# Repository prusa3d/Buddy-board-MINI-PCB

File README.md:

# Buddy-board-MINI-PCB

KiCad PCB layout

* [Interactive bom](http://htmlpreview.github.io/?https://github.com/prusa3d/Buddy-board-MINI-PCB/blob/master/rev.1.0.0/ibom.html)
* [STEP 3D model](rev.1.0.0/BUDDY_v1.0.0.step)

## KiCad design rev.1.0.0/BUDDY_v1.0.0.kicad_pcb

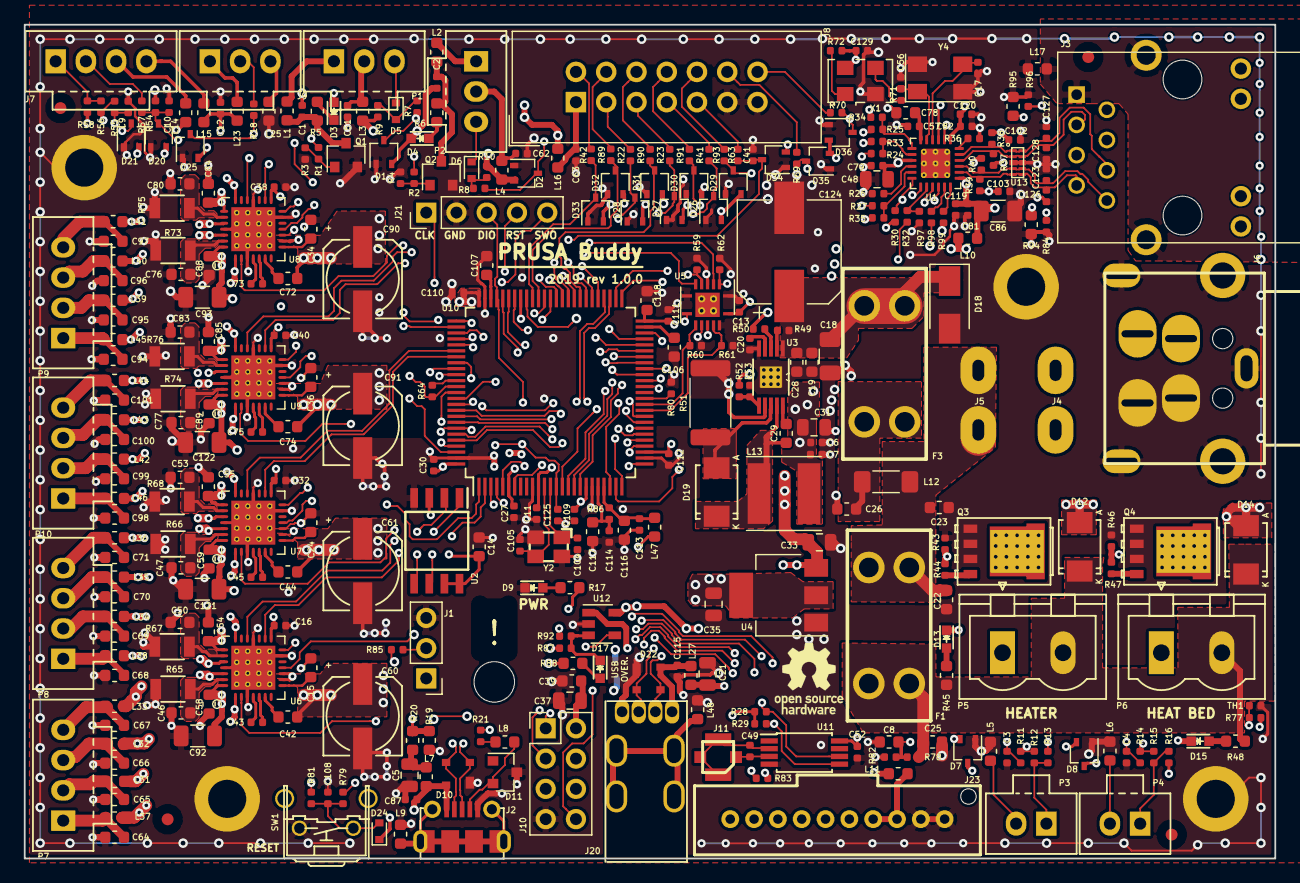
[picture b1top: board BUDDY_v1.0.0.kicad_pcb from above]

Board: 6 copper layers, 105.0 x 70.0 mm, 362 parts (1 on the bottom side), 245 nets.

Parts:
C1, C2, C3, C4, C6, C7, C9, C10, C11, C12, C13, C16, C27, C30, C32, C38, C40, C41, C51, C52, C62, C63, C79, C87, C102, C103, C108, C109, C110, C111, C112, C113, C114, C115, C119, C120, C125: 100n; C_0402_1005Metric
C5: 10u*; C_0805_2012Metric
C8, C14, C22, C23, C25, C26, C28, C29, C39, C42, C44, C46, C47, C50, C53, C54, C55, C58, C59, C72, C74, C76, C77, C80, C83, C84, C85, C88, C89: 100n; C_0603_1608Metric
C15, C24, C34, C36: 4.7uF; C_0603_1608Metric
C17, C56: 30p; C_0402_1005Metric
C18: 4u7; C_1206_3216Metric
C19, C78, C117: 1u; C_0603_1608Metric
C20: 4n7; C_0402_1005Metric
C21: 4u7; C_0805_2012Metric
C31, C33, C35, C37, C48: 10u; C_0805_2012Metric
C43, C45, C73, C75: 22n; C_0402_1005Metric
C49: 10p*; C_0402_1005Metric
C57: 470p; C_0402_1005Metric
C60, C61, C90, C91: 100u; c_elec_6.3x7.7
C64, C65, C66, C67, C68, C69, C70, C71, C94, C95, C96, C97, C98, C99, C100, C101: 1n; C_0603_1608Metric
C81, C82: 10n; C_0402_1005Metric
C86: 100u; C_1206_3216Metric
C92, C93, C121, C122: 10u; C_1206_3216Metric
C104, C105, C123, C126, C127, C128: 10p; C_0402_1005Metric
C106, C107: 2,2u; C_0603_1608Metric
C116, C118: 10u; C_0603_1608Metric
C124: 330u; CP_Elec_8x10.5
C129: 10n*; C_0402_1005Metric
D1, D2, D7, D8, D20, D21, D25, D26, D27, D28, D29, D30, D31, D32, D33, D34, D35, D36: BAV99W; SOT-323_SC-70
D3, D4, D9, D13, D15, D17: GRN; LED_0603
D5, D6, D24: BAT54KFILM; D_SOD-523
D10, D22: USBLC6-2P6; SOT143B
D11: ESDA6V1L; SOT-23
D12, D14: SK310A-TP; DO-214AC
D18: SMAJ28A; D_SMA
D19: SK310A; DO-214AC
F1, F3: KEYSTONE 3568; Fuse-Keystone-3557-2
F1-fuse1: fuse 7,5A; MEC
F3-fuse3: fuse 3A; MEC
J1: Conn_01x03; PinHeader_1x03_P2.54mm_Vertical
J1-jumper1: 2,54 jumper; MEC
J2: 105017-0001; USB-micro
J3: HR911105A
J4, J5: faston; faston-hole-m
J6: Mini-DIN-4-KPJX; KPJX-4S
J7: 70543-0003; Pin_1x04-XL
J8: 302-S141; IDC-Header_2x07_P2.54mm_Vertical
J9: 70543-0002; Pin_1x03-XL
J10: Conn_02x04_Odd_Even; PinHeader_2x04_P2.54mm_Vertical
J11: UFL coaxial; UFL-MOLEX-73412-0114
J12, J13, J14, J15: Conn_01x01; Fiducial_1mm_Dia_2.54mm_Outer_CopperTop
J16, J17, J18, J19: Conn_01x01; MountingHole_3.2mm_M3_ISO14580_Pad
J20: 67329-8000; USB-A-vertical-MX-67329-8000
J21: Conn_01x05; PinHeader_1x05_P2.54mm_Vertical
J23: Conn_01x10; MOLEX_559321010
JP1: Jumper; SolderJumper-2_P1.3mm_Open_TrianglePad1.0x1.5mm
L1, L2, L3, L4, L5, L6, L7, L8, L9, L10, L11, L14, L15, L16, L17, L23, L25, L27, L31, L32, L33, L34, L35, L36, L37, L38, L39, L40, L41, L42, L43, L44, L45, L46, L47, L48: BLM18KG121TN1D; R_0603_1608Metric
L12: BLM41PG600SN1L; R_1806_4516Metric
L13: 15uH; VLS6045EX
NT3, NT4: Net-Tie_2; NetTie-2_SMD_Pad0.5mm
P1, P2: 70543-0002; Pin_1x03-XL
P3, P4: 70543-0001; Pin_1x02-XL
P5, P6: TBG-5-PW-2P/GN; PhoenixContact_MSTBVA-G_02x5.08mm_Vertical
P7, P8, P9, P10: 70543-0003; Pin_1x04-XL
Q1, Q2: MMBF170; SOT-23
Q3, Q4: PSMN2R6-40YS; SOT-669_LFPAK_alternate-numbers_VIA
R1, R2, R18, R22, R23, R41, R42, R44, R47, R57, R63, R69, R70, R89, R90: 100R; R_0402_1005Metric
R3, R4, R43, R46, R49: 100k; R_0402_1005Metric
R5, R6: 2k2; R_0603_1608Metric
R7, R8, R9, R10, R55, R56, R59, R60, R61, R62: 1k8; R_0402_1005Metric
R11, R12, R14, R15: 2k37; R_0402_1005Metric
R13, R16, R58, R77, R80, R85: 4k7; R_0402_1005Metric
R17, R88, R94, R95: 620R; R_0603_1608Metric
R19: 1k; R_0603_1608Metric
R20: 2k; R_0603_1608Metric
R21, R64, R79, R82: 1k; R_0402_1005Metric
R24, R25, R27, R32, R98, R99: 33R; R_0402_1005Metric
R26, R33, R34, R35, R50, R52, R53, R54, R78, R81, R84, R96: 10k; R_0402_1005Metric
R28, R29, R30: 1k5; R_0402_1005Metric
R36: 12k1; R_0402_1005Metric
R37, R38, R39, R40: 49.9R; R_0402_1005Metric
R45, R48: 10k; R_0603_1608Metric
R51: 60m; R_2512_6332Metric
R65, R66, R67, R68, R73, R74, R75, R76: R22; R_1206
R71: 100R*; R_0402_1005Metric
R72, R97: 10k*; R_0402_1005Metric
R83: 1k*; R_0402_1005Metric
R86, R92: 0R; R_0402_1005Metric
R87: 47k; R_0402_1005Metric
R91: 510R; R_0402_1005Metric
R93: 330R; R_0402_1005Metric
SW1: TACTA-64N-F; TACT-90
TH1: NTCG104LH104JTDS; R_0402_1005Metric
U1: LAN8742A-CZ-TR; VQFN-24-1EP_4x4mm_P0.5mm_EP2.45x2.45mm_ThermalVias
U2: W25Q64JVSSIQ; SOIC8-wide
U3: LM25011MY/NOPB; SOP50P490X110-11N
U4: NCP1117-3.3_SOT223; SOT-223-3_TabPin2
U5: AHCT125; Texas_S-PVQFN-N14_ThermalVias
U6, U7, U8, U9: TMC2209-LA; QFN-28_EP_5x5_Pitch0.5mm
U10: MCU-STM32F407VGT6(LQFP100); LQFP-100_14x14mm_P0.5mm
U11: ST25DV64K; TSSOP-8_4.4x3mm_P0.65mm
U12: STMPS2141STR; SOT-23-5
U13: DT1140-04LP
X1: ASE-xxxMHz*; Oscillator_SMD_EuroQuartz_XO53-4Pin_5.0x3.2mm
Y2: Crystal; Crystal-3.2x2.5mm
Y4: ECS-250-20-30B-AGL-TR; Crystal_SMD_Abracon_ABM3C-4Pin_5.0x3.2mm
apendix: apendix-1

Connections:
24V2: C25.1, D12.1, D14.1, F1.1, P5.2, P6.2, R45.2, R48.2, R78.1
+3V3: C11.1, C14.1, C16.2, C27.1, C30.1, C32.2, C35.1, C37.1, C38.2, C39.1, C40.2, C48.1, C52.1, C79.1, C109.1, C110.1, C111.1, C112.1, C118.1, C129.1, D7.2, D8.2, D21.2, D24.1, D34.2, J1.1, J10.2, J10.6, L10.2, L11.1, L47.1, R13.1, R16.1, R17.2, R28.2, R29.2, R30.1, R33.1, R34.1, R35.1, R58.1, R72.1, R77.1, R81.2, R87.1, R88.1, U1.9, U2.3, U2.7, U2.8, U4.2, U6.15, U7.9, U7.15, U8.10, U8.15, U9.9, U9.10, U9.15, U10.6, U10.11, U10.19, U10.28, U10.50, U10.75, U10.100, U11.8, X1.4
+5V: C1.2, C2.2, C6.1, C7.1, C12.1, C13.1, C31.1, C33.1, D1.2, D2.2, D3.2, D4.2, D20.2, D25.2, D26.2, D27.2, D28.2, D29.2, D30.2, D31.2, D32.2, D33.2, D35.2, D36.2, JP1.2, L3.1, L4.1, L13.2, L15.1, L16.1, L23.1, R9.2, R10.2, R50.2, R52.1, R54.2, U4.3, U5.14, U12.5
+24V: C22.1, C23.1, F1.2, J5.1, L12.1
+24VMOT: C18.1, C19.1, C28.1, C42.1, C44.1, C54.1, C55.1, C58.1, C59.1, C60.1, C61.1, C72.1, C74.1, C84.1, C85.1, C88.1, C89.1, C90.1, C91.1, C92.1, C93.1, C121.1, C122.1, C124.1, D18.1, F3.1, R49.1, U3.1, U6.22, U6.28, U7.22, U7.28, U8.22, U8.28, U9.22, U9.28
/CPU/BOOT0: NT3.1, R85.2, U10.94
/CPU/NRST: C41.1, C125.1, D34.3, J21.4, R63.2, R79.2, U10.14
/CPU/PA4_THERM-1: C4.2, R14.2, U10.29
/CPU/PA5_THERM-2: R77.2, TH1.1, U10.30
/CPU/PA6_THERM-PINDA: C9.2, R55.2, U10.31
/CPU/PA8_Z-MIN: C10.1, D20.3, R54.1, R57.2, U10.67
/CPU/PA9_USB-FS-VBUS: R19.1, R20.2, U10.68
/CPU/PA10_USB-FS-ID: R21.1, U10.69
/CPU/PB5: J23.2, U10.91
/CPU/PB8_SCL: J23.5, R28.1, U10.95, U11.6
/CPU/PB9_SDA: J23.6, R29.1, U10.96, U11.5
/CPU/PB10_SCK2: D30.3, R91.1, U10.47
/CPU/PC0_THERM-0: C3.2, R11.2, U10.15
/CPU/PC10_SCK: U2.6, U10.78
/CPU/PD0_X-DIR: U7.19, U10.81
/CPU/PD1_X-STEP: U7.16, U10.82
/CPU/PD2_Z-EN: U6.2, U10.83
/CPU/PD3_X-EN: U7.2, U10.84
/CPU/PD4_Z-STEP: U6.16, U10.85
/CPU/PD12_Y-DIR: U9.19, U10.59
/CPU/PD13_Y-STEP: U9.16, U10.60
/CPU/PD14_Y-EN: U9.2, U10.61
/CPU/PD15_Z-DIR: U6.19, U10.62
/CPU/PE0: J23.1, U10.97
/CPU/PE1_Y-Diag: U9.11, U10.98
/CPU/PE2_X-Diag: U7.11, U10.1
/CPU/PE3_Z-Diag: U6.11, U10.2
/CPU/PE4_USB-HS-OVERCURRENT: R92.2, U10.3
/CPU/PE5_USB-HS-PWR-EN: U10.4, U12.4
/CPU/RX_1: J23.4, R83.1, U10.93
/CPU/SWCLK: J21.1, U10.76
/CPU/SWDIO: J21.3, NT4.1, U10.72
/CPU/SWO: J21.5, U10.89
/CPU/TX_1: J23.3, R83.2, U10.92
/CPU/VDDA: C113.1, C116.1, L47.2, R86.2, U10.22
/CPU/VREF+: C114.1, C117.1, R86.1, U10.21
/ETHERNET/EPHY_RST: U1.15, U10.39
/ETHERNET/ETH_LED1: J3.12, R96.1, U1.3
/ETHERNET/ETH_LED2: J3.9, R84.1, U1.2
/ETHERNET/ETH_RMII_CRS_DV: R27.1, U10.32
/ETHERNET/ETH_RMII_MDC: U1.13, U10.16
/ETHERNET/ETH_RMII_MDIO: R30.2, U1.12, U10.25
/ETHERNET/ETH_RMII_REF_CLK: R32.1, U10.24
/ETHERNET/ETH_RMII_RXD0: R24.1, U10.33
/ETHERNET/ETH_RMII_RXD1: R25.1, U10.34
/ETHERNET/ETH_RMII_TXD0: R98.1, U10.51
/ETHERNET/ETH_RMII_TXD1: R99.1, U10.52
/ETHERNET/ETH_RMII_TX_EN: U1.16, U10.48
/ETHERNET/RD_N: C128.1, J3.6, R37.2, U1.22, U13.2
/ETHERNET/RD_P: C127.1, J3.3, R38.2, U1.23, U13.1
/ETHERNET/TD_N: C126.1, J3.2, R39.2, U1.20, U13.5
/ETHERNET/TD_P: C123.1, J3.1, R40.2, U1.21, U13.4
/FANS/FAN-0-TACH: D1.3, R7.1, U10.41
/FANS/FAN-1-TACH: D2.3, R8.1, U10.45
/FLASH/FLASH-CSN: U2.1, U10.88
/FLASH/MISO: U2.2, U10.79
/FLASH/MOSI: U2.5, U10.80
/LEVEL_CONVERTER/BED-HEAT: R61.2, U5.12, U10.35
/LEVEL_CONVERTER/FAN-0: R62.2, U5.2, U10.42
/LEVEL_CONVERTER/FAN-1: R59.2, U5.5, U10.40
/LEVEL_CONVERTER/HEAT-0: R60.2, U5.9, U10.36
/PERIPHERALS/ESP-GPIO0: J10.3, U10.5
/PERIPHERALS/ESP-RST: J10.4, U10.7
/PERIPHERALS/ESP-Rx: J10.1, U10.63
/PERIPHERALS/ESP-Tx: J10.8, U10.64
/PERIPHERALS/FILAMENT_SENSOR: D25.3, R18.2, U10.90
/PERIPHERALS/LCD-BUZZER: D36.3, R70.1, U10.23
/PERIPHERALS/LCD-CS: D33.3, R42.1, U10.66
/PERIPHERALS/LCD-RS: D31.3, R90.1, U10.58
/PERIPHERALS/LCD-RST: D32.3, R89.1, U10.65
/PERIPHERALS/LCD-SW1: D28.3, R22.2, U10.43
/PERIPHERALS/LCD-SW2: D27.3, R23.2, U10.46
/PERIPHERALS/LCD-SW3: D26.3, R41.2, U10.44
/PERIPHERALS/MISO2: D35.3, R69.1, U10.17
/PERIPHERALS/MOSI2: D29.3, R93.1, U10.18
/POWER/BED_MON: C8.1, R78.2, R82.1, U10.26
/Trinamic driver/E-DIR: U8.19, U10.55
/Trinamic driver/E-Diag: U8.11, U10.77
/Trinamic driver/E-EN: U8.2, U10.57
/Trinamic driver/E-Step: U8.16, U10.56
/Trinamic driver/MOT-UART: R64.1, U6.14, U7.14, U8.14, U9.14, U10.87
BED-HEAT-5V: R46.1, R47.1, U5.11
FAN-0-5V: R1.1, U5.3
FAN-1-5V: R2.1, U5.6
GND: C3.1, C4.1, C5.2, C6.2, C7.2, C8.2, C9.1, C10.2, C11.2, C12.2, C13.2, C14.2, C15.1, C16.1, C17.2, C18.2, C19.2, C20.2, C21.2, C22.2, C23.2, C24.1, C25.2, C26.2, C27.2, C28.2, C30.2, C31.2, C32.1, C33.2, C34.1, C35.2, C36.1, C37.2, C38.1, C39.2, C40.1, C41.2, C46.2, C47.2, C48.2, C50.2, C51.2, C52.2, C53.2, C54.2, C55.2, C56.2, C57.2, C58.2, C59.2, C60.2, C61.2, C62.2, C63.2, C64.1, C65.1, C66.1, C67.1, C68.1, C69.1, C70.1, C71.1, C76.2, C77.2, C78.2, C79.2, C80.2, C81.2, C82.2, C83.2, C84.2, C85.2, C86.2, C87.2, C88.2, C89.2, C90.2, C91.2, C92.2, C93.2, C94.1, C95.1, C96.1, C97.1, C98.1, C99.1, C100.1, C101.1, C102.2, C103.2, C104.2, C105.2, C106.2, C107.2, C108.2, C109.2, C110.2, C111.2, C112.2, C113.2, C114.2, C115.2, C116.2, C117.2, C118.2, C119.2, C120.2, C121.2, C122.2, C123.2, C124.2, C125.2, C126.2, C127.2, C128.2, C129.2, D1.1, D2.1, D7.1, D8.1, D9.1, D10.1, D11.3, D18.2, D20.1, D21.1, D22.1, D25.1, D26.1, D27.1, D28.1, D29.1, D30.1, D31.1, D32.1, D33.1, D34.1, D35.1, D36.1, J1.3, J2.5, J6.1, J6.3, J6.5, J6.6, J6.7, J6.8, J6.9, J8.11, J8.13, J10.7, J16.1, J17.1, J18.1, J19.1, J20.4, J21.2, J23.9, J23.10, L5.1, L6.1, L9.1, L14.1, L17.1, L25.1, L48.1, NT3.2, NT4.2, Q1.2, Q2.2, Q3.2, Q4.2, R3.2, R4.2, R19.2, R26.1, R36.2, R43.2, R46.2, R51.2, R53.2, R59.1, R60.1, R61.1, R62.1, R65.1, R66.1, R67.1, R68.1, R73.1, R74.1, R75.1, R76.1, R80.1, R82.2, R84.2, R94.1, R95.2, R96.2, R97.2, SW1.2, TH1.2, U1.25, U2.4, U3.5, U3.7, U3.11, U4.1, U5.1, U5.4, U5.7, U5.10, U5.13, U6.3, U6.9, U6.10, U6.13, U6.18, U6.25, U6.29, U7.3, U7.10, U7.13, U7.18, U7.25, U7.29, U8.3, U8.9, U8.13, U8.18, U8.25, U8.29, U9.3, U9.13, U9.18, U9.25, U9.29, U10.10, U10.20, U10.27, U10.74, U10.99, U11.4, U12.2, U13.3, X1.2, Y2.2, Y2.4, Y4.2, Y4.4
HEAT-0-5V: R43.1, R44.1, U5.8
unnamed: C1.1, L1.1, Q1.3, R5.1
unnamed: C2.1, L2.1, Q2.3, R6.1
unnamed: C5.1, L7.1, R20.1
unnamed: C15.2, U6.8
unnamed: C17.1, U1.4, Y4.3
unnamed: C20.1, U3.4
unnamed: C21.1, L27.1, U12.1
unnamed: C24.2, U7.8
unnamed: C26.1, F3.2, L12.2
unnamed: C29.1, U3.10
unnamed: C29.2, D19.1, L13.1, U3.9
unnamed: C34.2, U8.8
unnamed: C36.2, U9.8
unnamed: C42.2, U6.6
unnamed: C43.1, U6.4
unnamed: C43.2, U6.5
unnamed: C44.2, U7.6
unnamed: C45.1, U7.4
unnamed: C45.2, U7.5
unnamed: C46.1, R65.2, U6.27
unnamed: C47.1, R66.2, U7.27
unnamed: C49.1, J11.2, U11.2
unnamed: C49.2, J11.1, U11.3
unnamed: C50.1, R67.2, U6.23
unnamed: C51.1, L3.2, P1.2
unnamed: C53.1, R68.2, U7.23
unnamed: C56.1, R71.1, U1.5, Y4.1
unnamed: C57.1, C78.1, U1.6
unnamed: C62.1, L4.2, P2.2
unnamed: C63.1, J8.1, L16.2
unnamed: C64.2, L37.2, P7.1
unnamed: C65.2, L31.2, P7.2
unnamed: C66.2, L32.2, P7.3
unnamed: C67.2, L33.2, P7.4
unnamed: C68.2, L38.2, P8.1
unnamed: C69.2, L34.2, P8.2
unnamed: C70.2, L35.2, P8.3
unnamed: C71.2, L36.2, P8.4
unnamed: C72.2, U8.6
unnamed: C73.1, U8.4
unnamed: C73.2, U8.5
unnamed: C74.2, U9.6
unnamed: C75.1, U9.4
unnamed: C75.2, U9.5
unnamed: C76.1, R73.2, U8.27
unnamed: C77.1, R74.2, U9.27
unnamed: C80.1, R75.2, U8.23
unnamed: C83.1, R76.2, U9.23
unnamed: C87.1, D10.4, J2.1, JP1.1, L7.2
unnamed: C94.2, L45.2, P9.1
unnamed: C95.2, L39.2, P9.2
unnamed: C96.2, L40.2, P9.3
unnamed: C97.2, L41.2, P9.4
unnamed: C98.2, L46.2, P10.1
unnamed: C99.2, L42.2, P10.2
unnamed: C100.2, L43.2, P10.3
unnamed: C101.2, L44.2, P10.4
unnamed: C81.1, C82.1, C86.1, C102.1, C103.1, C119.1, C120.1, J3.4, J3.5, L10.1, R37.1, R38.1, R39.1, R40.1, U1.1, U1.19
unnamed: C104.1, U10.13, Y2.1
unnamed: C105.1, U10.12, Y2.3
unnamed: C106.1, U10.49
unnamed: C107.1, U10.73
unnamed: C108.1, D24.2, R79.1, R81.1, SW1.1
unnamed: C115.1, D22.4, J20.1, L27.2
unnamed: D3.1, R5.2
unnamed: D4.1, R6.2
unnamed: D5.1, P1.3
unnamed: D5.2, R7.2, R9.1
unnamed: D6.1, P2.3
unnamed: D6.2, R8.2, R10.1
unnamed: D7.3, R11.1, R12.2
unnamed: D8.3, R14.1, R15.2
unnamed: D9.2, R17.1
unnamed: D11.2, J2.4, L8.2
unnamed: D12.2, D13.1, P5.1, Q3.3
unnamed: D13.2, R45.1
unnamed: D14.2, D15.1, P6.1, Q4.3
unnamed: D15.2, R48.1
unnamed: D17.1, R87.2, R92.1, U12.3
unnamed: D17.2, R88.2
unnamed: D19.2, R51.1, U3.8
unnamed: D21.3, R55.1, R56.2
unnamed: J1.2, R85.1
unnamed: J2.6, L9.2
unnamed: J3.10, R94.2
unnamed: J3.11, R95.1
unnamed: J3.8, J3.13, L17.2
unnamed: J4.1, J6.2, J6.4
unnamed: J7.1, R56.1, R58.2
unnamed: J7.2, R57.1
unnamed: J7.3, L14.2
unnamed: J7.4, L15.2
unnamed: J8.2, R42.2
unnamed: J8.3, R22.1
unnamed: J8.4, R89.2
unnamed: J8.5, R23.1
unnamed: J8.6, R90.2
unnamed: J8.7, R41.1
unnamed: J8.8, R91.2
unnamed: J8.9, R63.1
unnamed: J8.10, R93.2
unnamed: J8.12, R69.2
unnamed: J8.14, R70.2
unnamed: J9.1, L23.2
unnamed: J9.2, R18.1
unnamed: J9.3, L25.2
unnamed: J20.5, L48.2
unnamed: J23.7, J23.8, L11.2
unnamed: L1.2, P1.1
unnamed: L2.2, P2.1
unnamed: L5.2, P3.2
unnamed: L6.2, P4.2
unnamed: L8.1, R21.2
unnamed: L31.1, U6.26
unnamed: L32.1, U6.24
unnamed: L33.1, U6.21
unnamed: L34.1, U7.26
unnamed: L35.1, U7.24
unnamed: L36.1, U7.21
unnamed: L37.1, U6.1
unnamed: L38.1, U7.1
unnamed: L39.1, U8.26
unnamed: L40.1, U8.24
unnamed: L41.1, U8.21
unnamed: L42.1, U9.26
unnamed: L43.1, U9.24
unnamed: L44.1, U9.21
unnamed: L45.1, U8.1
unnamed: L46.1, U9.1
unnamed: P3.1, R12.1, R13.2
unnamed: P4.1, R15.1, R16.2
unnamed: Q1.1, R1.2, R3.1
unnamed: Q2.1, R2.2, R4.1
unnamed: Q3.1, R44.2
unnamed: Q4.1, R47.2
unnamed: R24.2, R33.2, U1.8
unnamed: R25.2, R34.2, U1.7
unnamed: R26.2, U1.10
unnamed: R27.2, R35.2, U1.11
unnamed: R32.2, R97.1, U1.14
unnamed: R36.1, U1.24
unnamed: R49.2, U3.2
unnamed: R50.1, U3.3
unnamed: R52.2, R53.1, U3.6
unnamed: R64.2, U10.86
unnamed: R71.2, X1.3
unnamed: R72.2, X1.1
unnamed: R80.2, U10.37
unnamed: R98.2, U1.17
unnamed: R99.2, U1.18
USB-FS_N: D10.3, J2.2, U10.70
USB-FS_P: D10.2, J2.3, U10.71
USB-HS_N: D22.3, J20.2, U10.53
USB-HS_P: D22.2, J20.3, U10.54

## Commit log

2023-06-03 update to new kicad

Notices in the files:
rev.1.0.0/BUDDY_v1.0.0.kicad_pcb:
http://creativecommons.org/licenses/by-sa/4.0
Licensed under the Attribution-ShareAlike 4.0 International (CC BY-SA 4.0)
